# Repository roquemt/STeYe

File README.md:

# STeYe
Flight computer for rocket competition. 

This flight computer is designed for high-performance rocketry competitions, offering precise measurement and control for various flight parameters. The system integrates a range of sensors and features to ensure reliable data acquisition and communication throughout the flight. It is built with flexibility, durability, and scalability in mind for a variety of mission profiles.

Key Features:

-  Accelerometers: Dual-range accelerometers (+/-16g and +/-200g) for accurate low and high-g-force measurement during flight.
-  Pressure Sensor: Atmospheric pressure monitoring for altitude and environmental data.
-  Humidity & Temperature Sensor: Measures environmental conditions critical for flight analysis.
-  Magnetometer: Provides orientation and heading information by sensing the Earth’s magnetic field.
-  Current Sensor: Tracks power consumption for optimized energy management.
-  Camera Interface (FPC): Supports OV5640 camera for video and image capture during flight.
-  WiFi & Bluetooth: Wireless communication for data transfer and real-time telemetry.
-  GNSS (Global Navigation Satellite System): Provides accurate positioning data for tracking and flight path monitoring.
-  LoRa: Long-range, low-power communication capability for telemetry.
-  Pyro Channel: Single pyro channel for controlled deployment of parachutes or other pyrotechnic devices.
-  Motor Control: Supports either one dual-coil stepper motor or up to four servomotors, operating between 5V and 12V for mechanical actuation.
-  Passive Buzzer: Provides audio alerts for critical status or events.
-  LED Indicators: Visual feedback for power, status, and activity.
-  Memory: Includes both flash storage and microSD for data logging and flight data retention.

Carrier Board (sensors and peripherals)

M.2 Board (Microcontrollers and Wifi)

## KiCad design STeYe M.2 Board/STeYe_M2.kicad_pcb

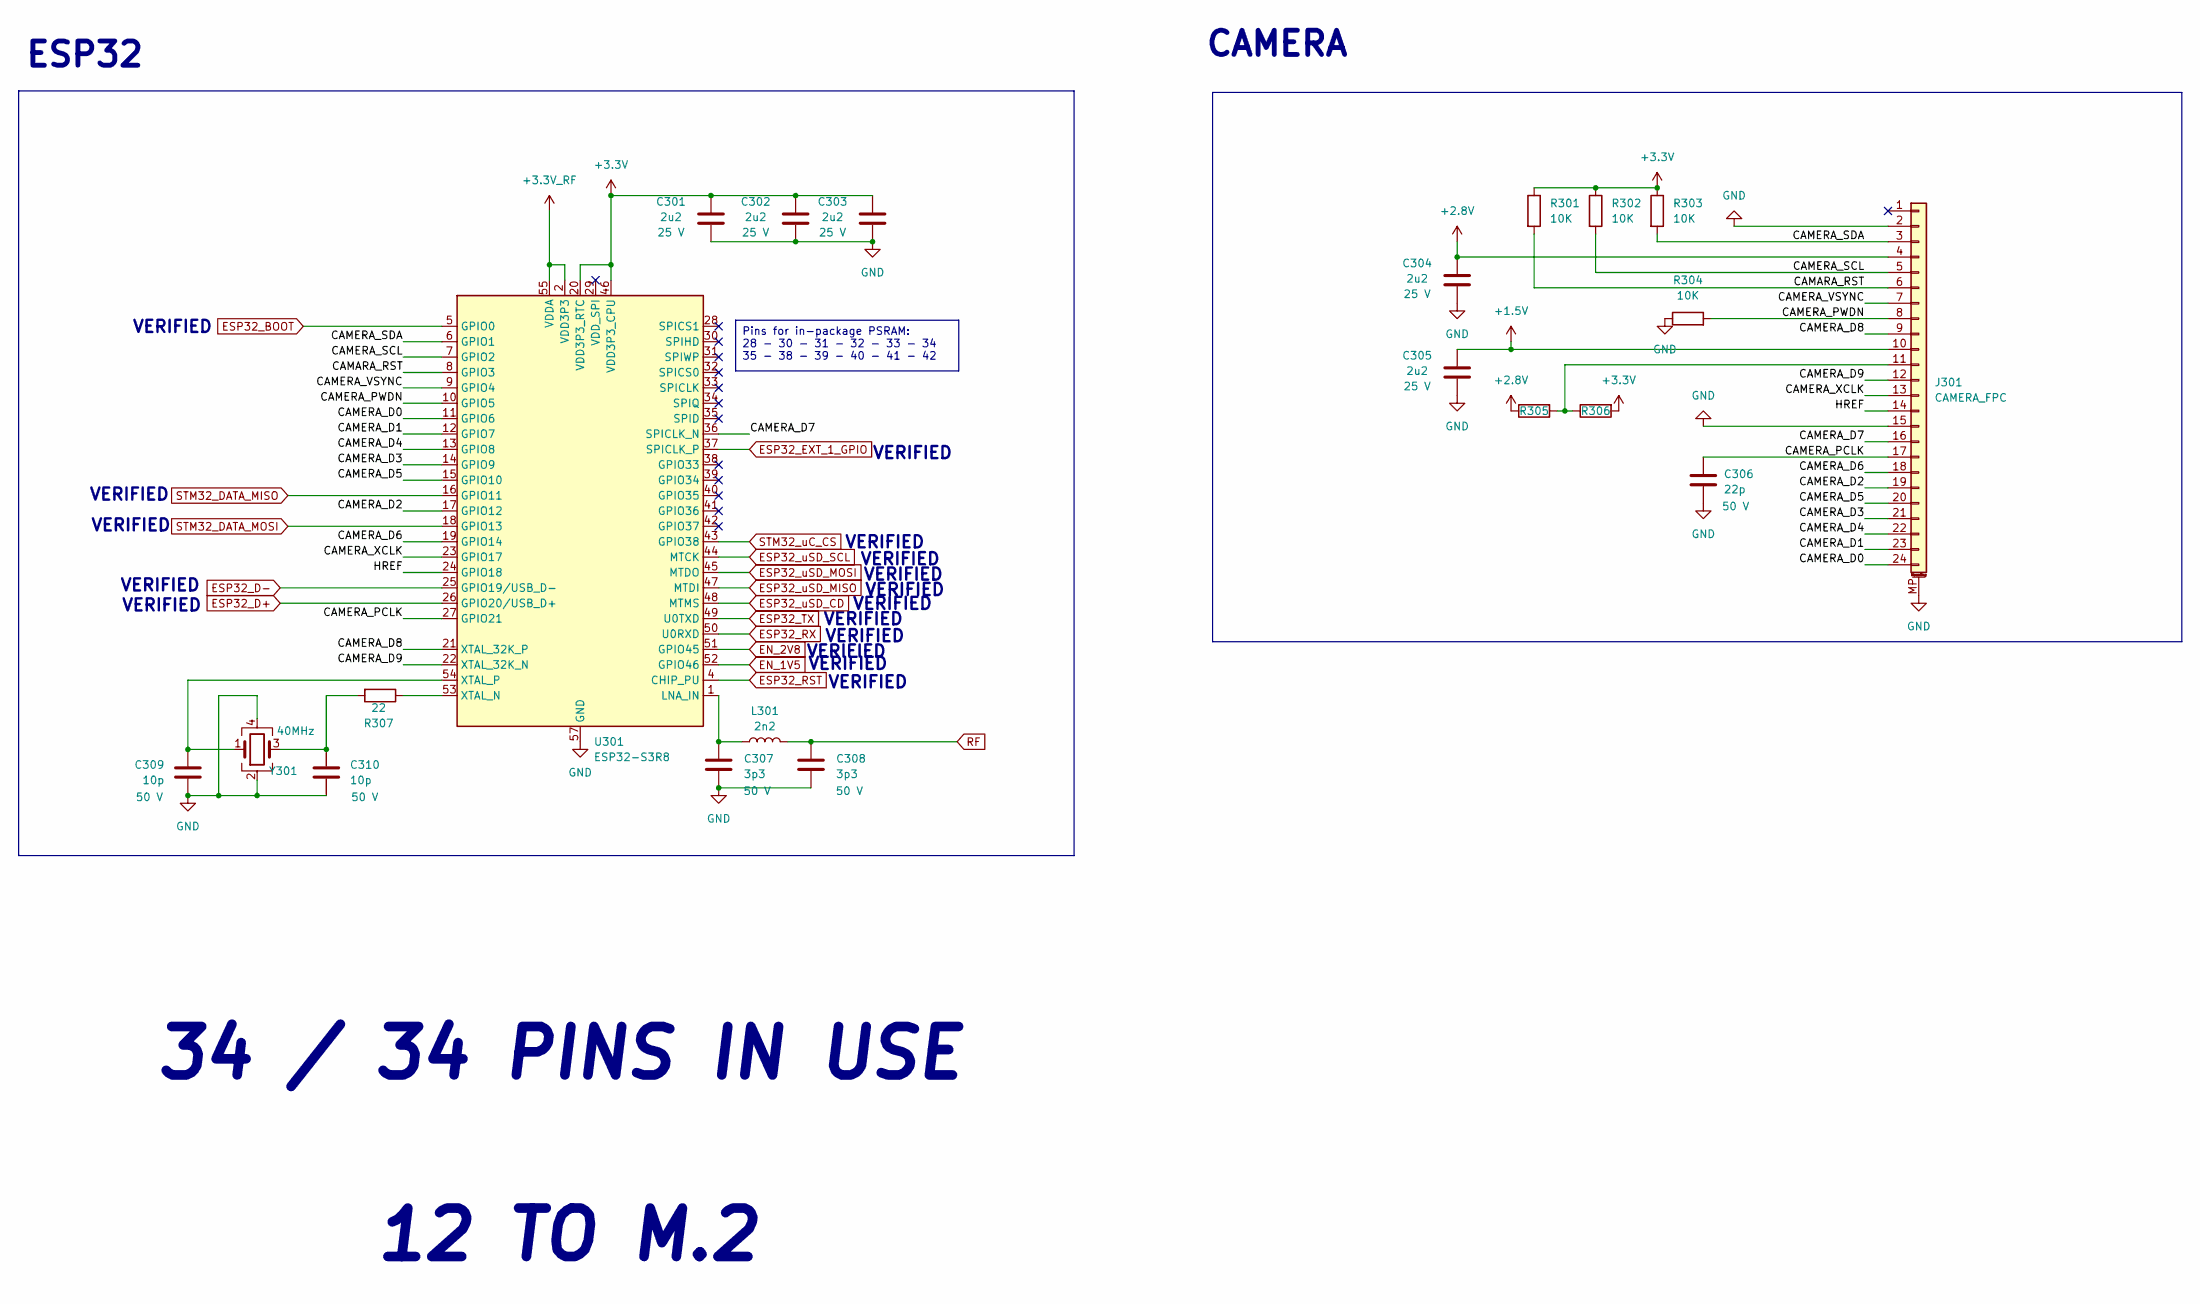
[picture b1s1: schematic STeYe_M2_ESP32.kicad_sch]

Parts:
C301, C302, C303, C304, C305: 2u2; C_0402_1005Metric; Voltage 25 V
C306: 22p; C_0402_1005Metric; Voltage 50 V
C307, C308: 3p3; C_0402_1005Metric; Voltage 50 V
C309, C310: 10p; C_0402_1005Metric; Voltage 50 V
J301: CAMERA_FPC; Hirose_FH12-24S-0.5SH_1x24-1MP_P0.50mm_Horizontal
L301: 2n2; Inductor
R301, R302, R303, R304: 10K; R_0402_1005Metric
R305, R306: R_0402_1005Metric
R307: 22; R_0402_1005Metric
U301: ESP32-S3R8; QFN-56-1EP_7x7mm_P0.4mm_EP4x4mm
Y301: 40MHz; Crystal_SMD_2016-4Pin_2.0x1.6mm

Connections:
+1.5V: C305.2, J301.10; also elsewhere on the board
+2.8V: C304.2, J301.4, R305.1; also elsewhere on the board
+3.3V: C301.2, C302.2, C303.2, R301.1, R302.1, R303.1, R306.2, U301.20 (VDD3P3_RTC), U301.46 (VDD3P3_CPU); also elsewhere on the board
+3.3V_RF: U301.2 (VDD3P3), U301.3 (VDD3P3), U301.55 (VDDA), U301.56 (VDDA); also elsewhere on the board
/ESP32/CAMARA_RST: J301.6, R301.2, U301.8 (GPIO3)
/ESP32/CAMERA_D0: J301.24, U301.11 (GPIO6)
/ESP32/CAMERA_D1: J301.23, U301.12 (GPIO7)
/ESP32/CAMERA_D2: J301.19, U301.17 (GPIO12)
/ESP32/CAMERA_D3: J301.21, U301.14 (GPIO9)
/ESP32/CAMERA_D4: J301.22, U301.13 (GPIO8)
/ESP32/CAMERA_D5: J301.20, U301.15 (GPIO10)
/ESP32/CAMERA_D6: J301.18, U301.19 (GPIO14)
/ESP32/CAMERA_D7: J301.16, U301.36 (SPICLK_N)
/ESP32/CAMERA_D8: J301.9, U301.21 (XTAL_32K_P)
/ESP32/CAMERA_D9: J301.12, U301.22 (XTAL_32K_N)
/ESP32/CAMERA_PCLK: C306.2, J301.17, U301.27 (GPIO21)
/ESP32/CAMERA_PWDN: J301.8, R304.2, U301.10 (GPIO5)
/ESP32/CAMERA_SCL: J301.5, R302.2, U301.7 (GPIO2)
/ESP32/CAMERA_SDA: J301.3, R303.2, U301.6 (GPIO1)
/ESP32/CAMERA_VSYNC: J301.7, U301.9 (GPIO4)
/ESP32/CAMERA_XCLK: J301.13, U301.23 (GPIO17)
/ESP32/HREF: J301.14, U301.24 (GPIO18)
EN_1V5: U301.52 (GPIO46); also elsewhere on the board
EN_2V8: U301.51 (GPIO45); also elsewhere on the board
ESP32_BOOT: U301.5 (GPIO0); also elsewhere on the board
ESP32_D+: U301.26 (GPIO20/USB_D+); also elsewhere on the board
ESP32_D-: U301.25 (GPIO19/USB_D-); also elsewhere on the board
ESP32_EXT_1_GPIO: U301.37 (SPICLK_P); also elsewhere on the board
ESP32_RST: U301.4 (CHIP_PU); also elsewhere on the board
ESP32_RX: U301.50 (U0RXD); also elsewhere on the board
ESP32_TX: U301.49 (U0TXD); also elsewhere on the board
ESP32_uSD_CD: U301.48 (MTMS); also elsewhere on the board
ESP32_uSD_MISO: U301.47 (MTDI); also elsewhere on the board
ESP32_uSD_MOSI: U301.45 (MTDO); also elsewhere on the board
ESP32_uSD_SCL: U301.44 (MTCK); also elsewhere on the board
GND: C301.1, C302.1, C303.1, C304.1, C305.1, C306.1, C307.2, C308.2, C309.2, C310.2, J301.2, J301.15, J301.MP (MountPin), R304.1, U301.57 (GND), Y301.2, Y301.4; also elsewhere on the board
unnamed: C310.1, R307.2, Y301.3
unnamed: J301.11, R305.2, R306.1
unnamed: C307.1, L301.1, U301.1 (LNA_IN)
unnamed: R307.1, U301.53 (XTAL_N)
unnamed: C309.1, U301.54 (XTAL_P), Y301.1
RF: C308.1, L301.2; also elsewhere on the board
STM32_DATA_MISO: U301.16 (GPIO11); also elsewhere on the board
STM32_DATA_MOSI: U301.18 (GPIO13); also elsewhere on the board
STM32_uC_CS: U301.43 (GPIO38); also elsewhere on the board

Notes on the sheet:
Pins for in-package PSRAM: 28 - 30 - 31 - 32 - 33 - 34 35 - 38 - 39 - 40 - 41 - 42
ESP32
VERIFIED
12 TO M.2
CAMERA
34 / 34 PINS IN USE

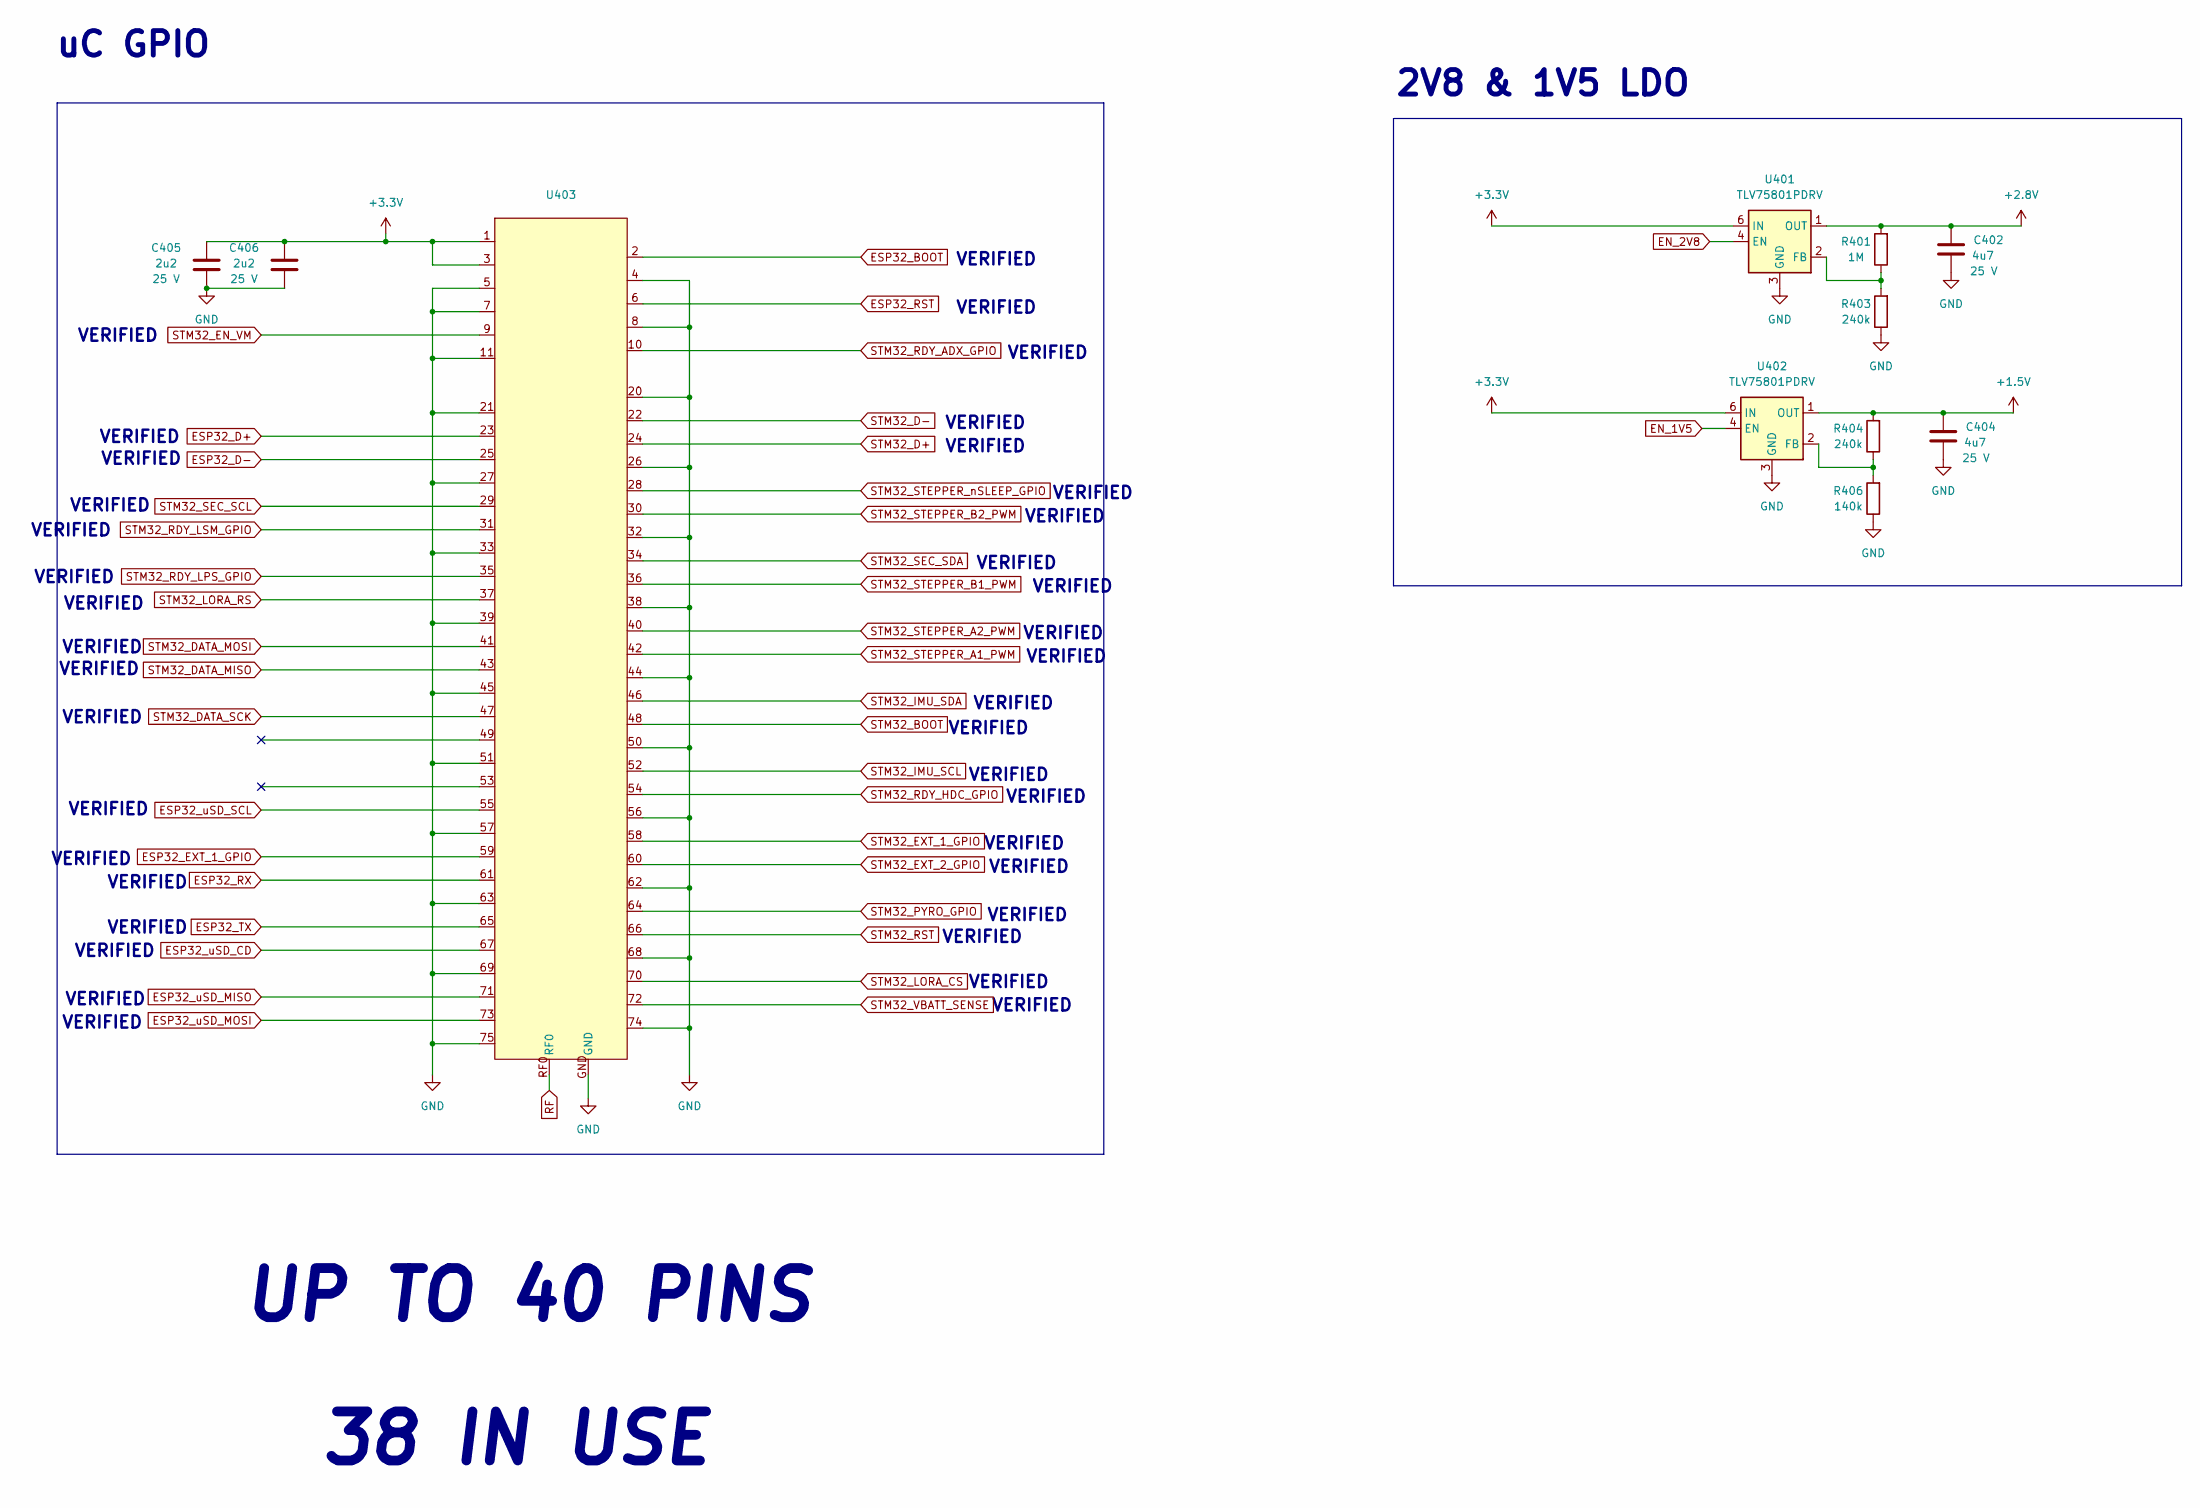
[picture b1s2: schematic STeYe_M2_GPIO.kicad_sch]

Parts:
C402, C404: 4u7; C_0402_1005Metric; Voltage 25 V
C405, C406: 2u2; C_0402_1005Metric; Voltage 25 V
R401: 1M; R_0402_1005Metric
R403, R404: 240k; R_0402_1005Metric
R406: 140k; R_0402_1005Metric
U401, U402: TLV75801PDRV; WSON-6-1EP_2x2mm_P0.65mm_EP1x1.6mm
U403: M.2-B-KEY_Antenna_1

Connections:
+1.5V: C404.1, R404.2, U402.1 (OUT); also elsewhere on the board
+2.8V: C402.1, R401.2, U401.1 (OUT); also elsewhere on the board
+3.3V: C405.2, C406.2, U401.6 (IN), U402.6 (IN), U403.1, U403.3; also elsewhere on the board
EN_1V5: U402.4 (EN); also elsewhere on the board
EN_2V8: U401.4 (EN); also elsewhere on the board
ESP32_BOOT: U403.2; also elsewhere on the board
ESP32_D+: U403.23; also elsewhere on the board
ESP32_D-: U403.25; also elsewhere on the board
ESP32_EXT_1_GPIO: U403.59; also elsewhere on the board
ESP32_RST: U403.6; also elsewhere on the board
ESP32_RX: U403.61; also elsewhere on the board
ESP32_TX: U403.65; also elsewhere on the board
ESP32_uSD_CD: U403.67; also elsewhere on the board
ESP32_uSD_MISO: U403.71; also elsewhere on the board
ESP32_uSD_MOSI: U403.73; also elsewhere on the board
ESP32_uSD_SCL: U403.55; also elsewhere on the board
GND: C402.2, C404.2, C405.1, C406.1, R403.1, R406.1, U401.3 (GND), U401.7 (GND), U402.3 (GND), U402.7 (GND), U403.4, U403.5, U403.7, U403.8, U403.11, U403.20, U403.21, U403.26, U403.27, U403.32, U403.33, U403.38, U403.39, U403.44, U403.45, U403.50, U403.51, U403.56, U403.57, U403.62, U403.63, U403.68, U403.69, U403.74, U403.75, U403.GND; also elsewhere on the board
unnamed: R401.1, R403.2, U401.2 (FB)
unnamed: R404.1, R406.2, U402.2 (FB)
RF: U403.RF0; also elsewhere on the board
STM32_BOOT: U403.48; also elsewhere on the board
STM32_D+: U403.24; also elsewhere on the board
STM32_D-: U403.22; also elsewhere on the board
STM32_DATA_MISO: U403.43; also elsewhere on the board
STM32_DATA_MOSI: U403.41; also elsewhere on the board
STM32_DATA_SCK: U403.47; also elsewhere on the board
STM32_EN_VM: U403.9; also elsewhere on the board
STM32_EXT_1_GPIO: U403.58; also elsewhere on the board
STM32_EXT_2_GPIO: U403.60; also elsewhere on the board
STM32_IMU_SCL: U403.52; also elsewhere on the board
STM32_IMU_SDA: U403.46; also elsewhere on the board
STM32_LORA_CS: U403.70; also elsewhere on the board
STM32_LORA_RS: U403.37; also elsewhere on the board
STM32_PYRO_GPIO: U403.64; also elsewhere on the board
STM32_RDY_ADX_GPIO: U403.10; also elsewhere on the board
STM32_RDY_HDC_GPIO: U403.54; also elsewhere on the board
STM32_RDY_LPS_GPIO: U403.35; also elsewhere on the board
STM32_RDY_LSM_GPIO: U403.31; also elsewhere on the board
STM32_RST: U403.66; also elsewhere on the board
STM32_SEC_SCL: U403.29; also elsewhere on the board
STM32_SEC_SDA: U403.34; also elsewhere on the board
STM32_STEPPER_A1_PWM: U403.42; also elsewhere on the board
STM32_STEPPER_A2_PWM: U403.40; also elsewhere on the board
STM32_STEPPER_B1_PWM: U403.36; also elsewhere on the board
STM32_STEPPER_B2_PWM: U403.30; also elsewhere on the board
STM32_STEPPER_nSLEEP_GPIO: U403.28; also elsewhere on the board
STM32_VBATT_SENSE: U403.72; also elsewhere on the board

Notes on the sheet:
VERIFIED
UP TO 40 PINS
uC GPIO
2V8 & 1V5 LDO
38 IN USE

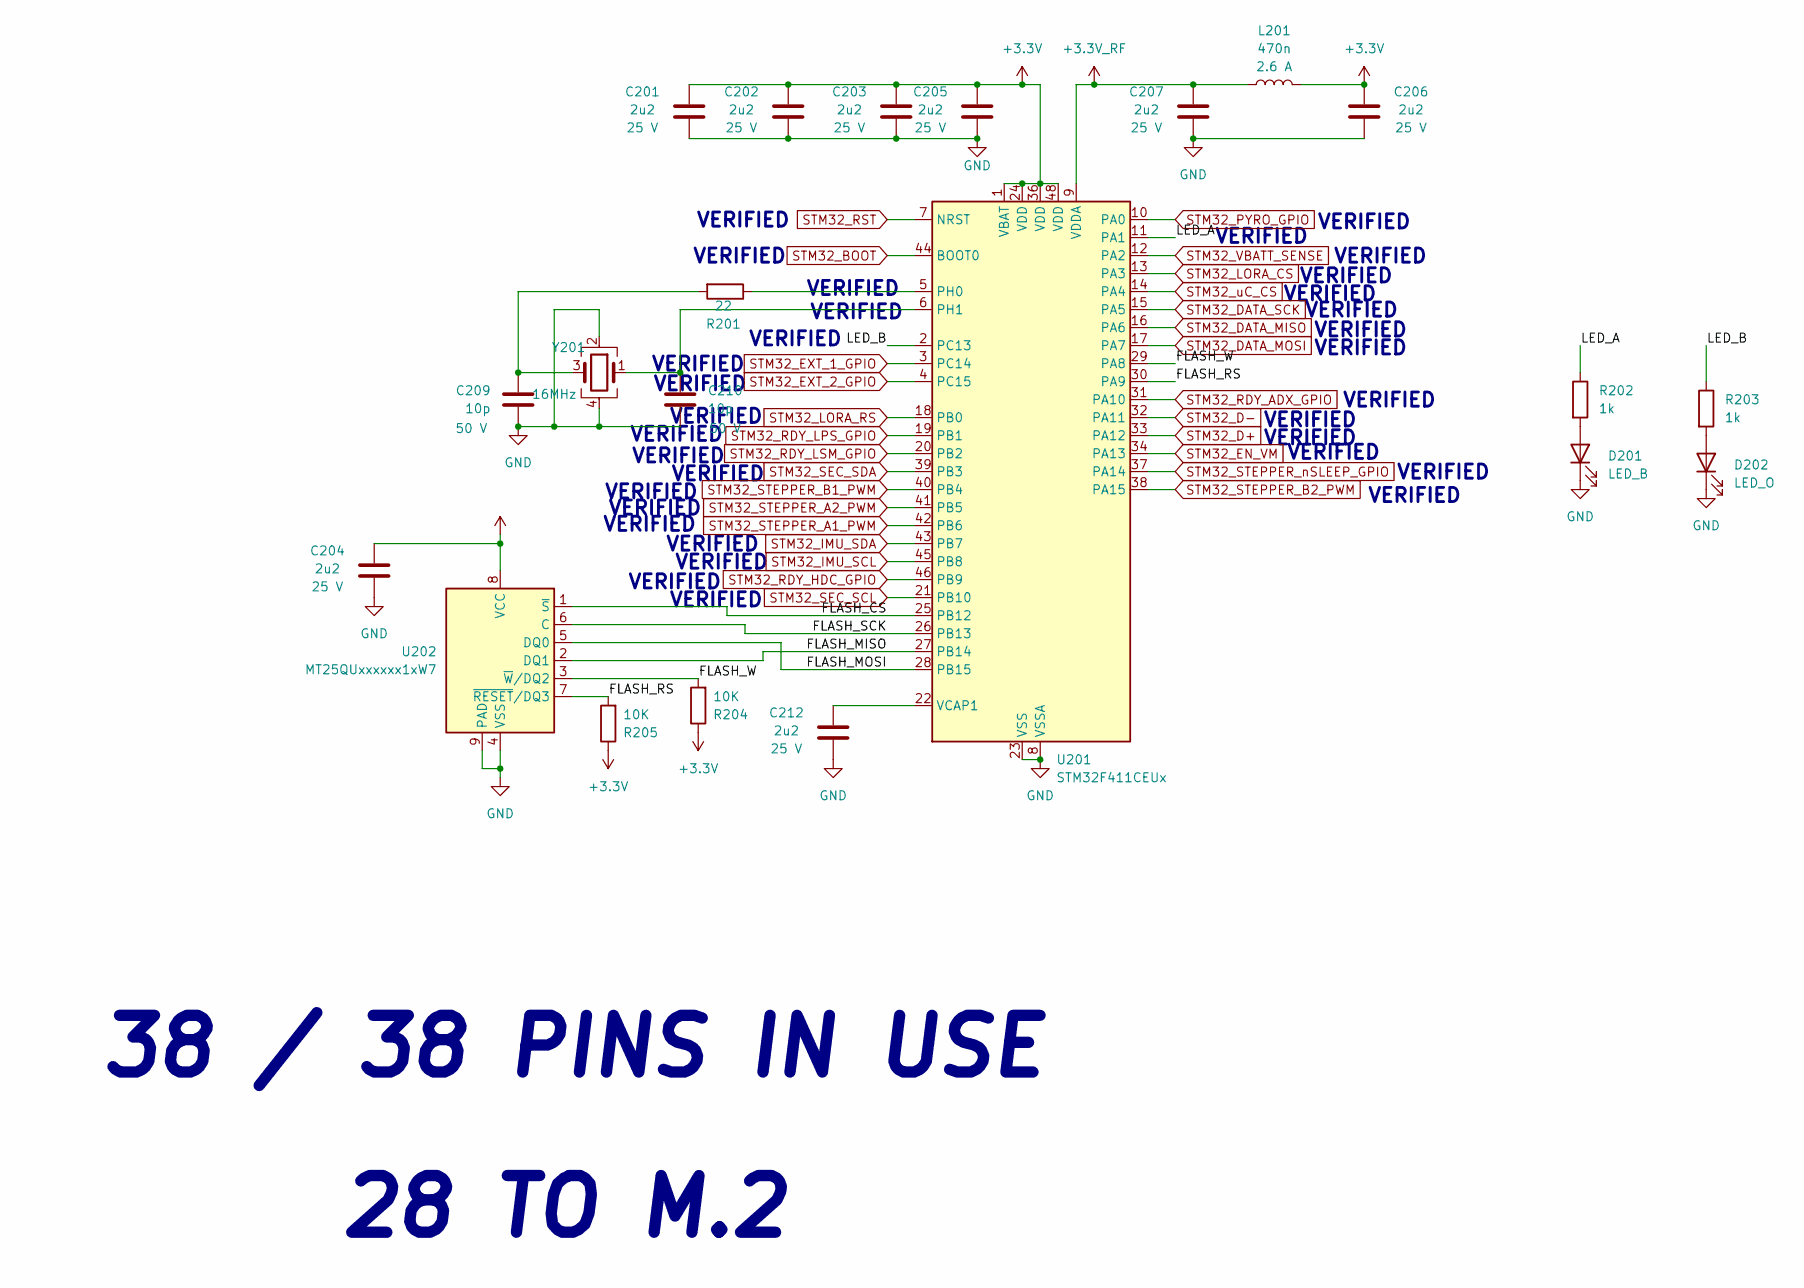
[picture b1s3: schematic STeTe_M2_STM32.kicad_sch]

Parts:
C201, C202, C203, C204, C205, C206, C207, C212: 2u2; C_0402_1005Metric; Voltage 25 V
C209, C210: 10p; C_0402_1005Metric; Voltage 50 V
D201: LED_B; D_0603_1608Metric
D202: LED_O; D_0603_1608Metric
L201: 470n; L_0603_1608Metric
R201: 22; R_0402_1005Metric
R202, R203: 1k; R_0402_1005Metric
R204, R205: 10K; R_0402_1005Metric
U201: STM32F411CEUx; QFN-48-1EP_7x7mm_P0.5mm_EP5.6x5.6mm
U202: MT25QUxxxxxx1xW7; W-PDFN-8-1EP_6x5mm_P1.27mm_EP3x3mm
Y201: 16MHz; Crystal_SMD_2016-4Pin_2.0x1.6mm

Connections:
+3.3V: C201.2, C202.2, C203.2, C204.2, C205.2, C206.2, L201.2, R204.1, R205.1, U201.1 (VBAT), U201.24 (VDD), U201.36 (VDD), U201.48 (VDD), U202.8 (VCC); also elsewhere on the board
+3.3V_RF: C207.2, L201.1, U201.9 (VDDA); also elsewhere on the board
/STM32/FLASH_CS: U201.25 (PB12), U202.1 (~S)
/STM32/FLASH_MISO: U201.27 (PB14), U202.2 (DQ1)
/STM32/FLASH_MOSI: U201.28 (PB15), U202.5 (DQ0)
/STM32/FLASH_RS: R205.2, U201.30 (PA9), U202.7 (~RESET/DQ3)
/STM32/FLASH_SCK: U201.26 (PB13), U202.6 (C)
/STM32/FLASH_W: R204.2, U201.29 (PA8), U202.3 (~W/DQ2)
/STM32/LED_A: R202.1, U201.11 (PA1)
/STM32/LED_B: R203.1, U201.2 (PC13)
GND: C201.1, C202.1, C203.1, C204.1, C205.1, C206.1, C207.1, C209.2, C210.2, C212.1, D201.1 (K), D202.1 (K), U201.8 (VSSA), U201.23 (VSS), U201.35 (VSS), U201.47 (VSS), U201.49 (VSS), U202.4 (VSS), U202.9 (PAD), Y201.2, Y201.4; also elsewhere on the board
unnamed: C209.1, R201.2, Y201.3
unnamed: D201.2 (A), R202.2
unnamed: D202.2 (A), R203.2
unnamed: R201.1, U201.5 (PH0)
unnamed: C210.1, U201.6 (PH1), Y201.1
unnamed: C212.2, U201.22 (VCAP1)
STM32_BOOT: U201.44 (BOOT0); also elsewhere on the board
STM32_D+: U201.33 (PA12); also elsewhere on the board
STM32_D-: U201.32 (PA11); also elsewhere on the board
STM32_DATA_MISO: U201.16 (PA6); also elsewhere on the board
STM32_DATA_MOSI: U201.17 (PA7); also elsewhere on the board
STM32_DATA_SCK: U201.15 (PA5); also elsewhere on the board
STM32_EN_VM: U201.34 (PA13); also elsewhere on the board
STM32_EXT_1_GPIO: U201.3 (PC14); also elsewhere on the board
STM32_EXT_2_GPIO: U201.4 (PC15); also elsewhere on the board
STM32_IMU_SCL: U201.45 (PB8); also elsewhere on the board
STM32_IMU_SDA: U201.43 (PB7); also elsewhere on the board
STM32_LORA_CS: U201.13 (PA3); also elsewhere on the board
STM32_LORA_RS: U201.18 (PB0); also elsewhere on the board
STM32_PYRO_GPIO: U201.10 (PA0); also elsewhere on the board
STM32_RDY_ADX_GPIO: U201.31 (PA10); also elsewhere on the board
STM32_RDY_HDC_GPIO: U201.46 (PB9); also elsewhere on the board
STM32_RDY_LPS_GPIO: U201.19 (PB1); also elsewhere on the board
STM32_RDY_LSM_GPIO: U201.20 (PB2); also elsewhere on the board
STM32_RST: U201.7 (NRST); also elsewhere on the board
STM32_SEC_SCL: U201.21 (PB10); also elsewhere on the board
STM32_SEC_SDA: U201.39 (PB3); also elsewhere on the board
STM32_STEPPER_A1_PWM: U201.42 (PB6); also elsewhere on the board
STM32_STEPPER_A2_PWM: U201.41 (PB5); also elsewhere on the board
STM32_STEPPER_B1_PWM: U201.40 (PB4); also elsewhere on the board
STM32_STEPPER_B2_PWM: U201.38 (PA15); also elsewhere on the board
STM32_STEPPER_nSLEEP_GPIO: U201.37 (PA14); also elsewhere on the board
STM32_VBATT_SENSE: U201.12 (PA2); also elsewhere on the board
STM32_uC_CS: U201.14 (PA4); also elsewhere on the board

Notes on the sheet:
VERIFIED
28 TO M.2
38 / 38 PINS IN USE

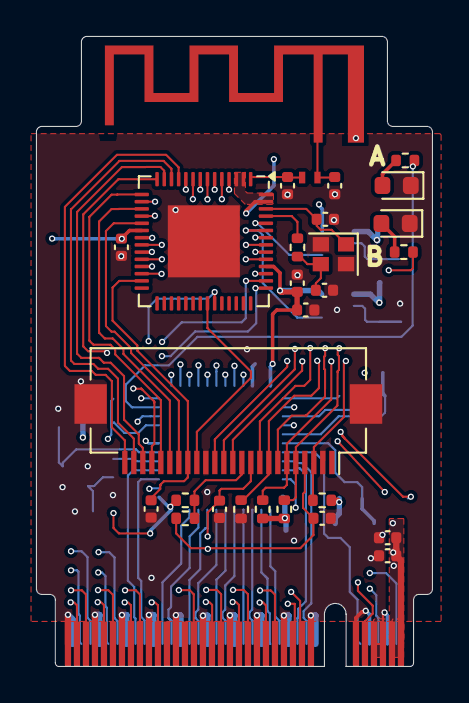
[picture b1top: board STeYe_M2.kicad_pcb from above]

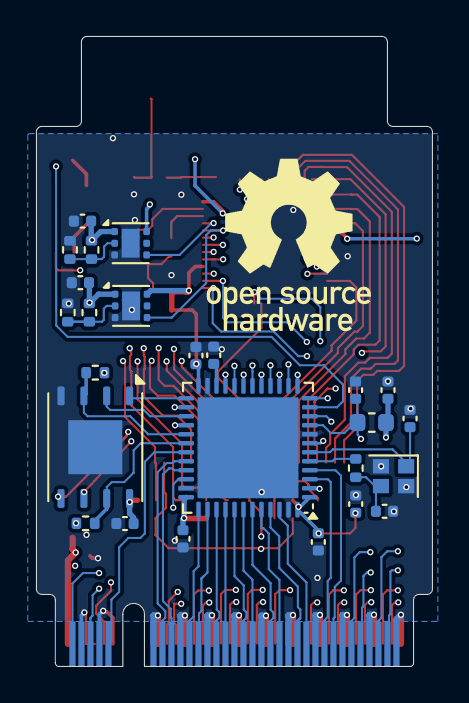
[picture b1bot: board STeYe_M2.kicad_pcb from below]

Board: 8 copper layers, 22.0 x 35.0 mm, 53 parts (25 on the bottom side), 86 nets.

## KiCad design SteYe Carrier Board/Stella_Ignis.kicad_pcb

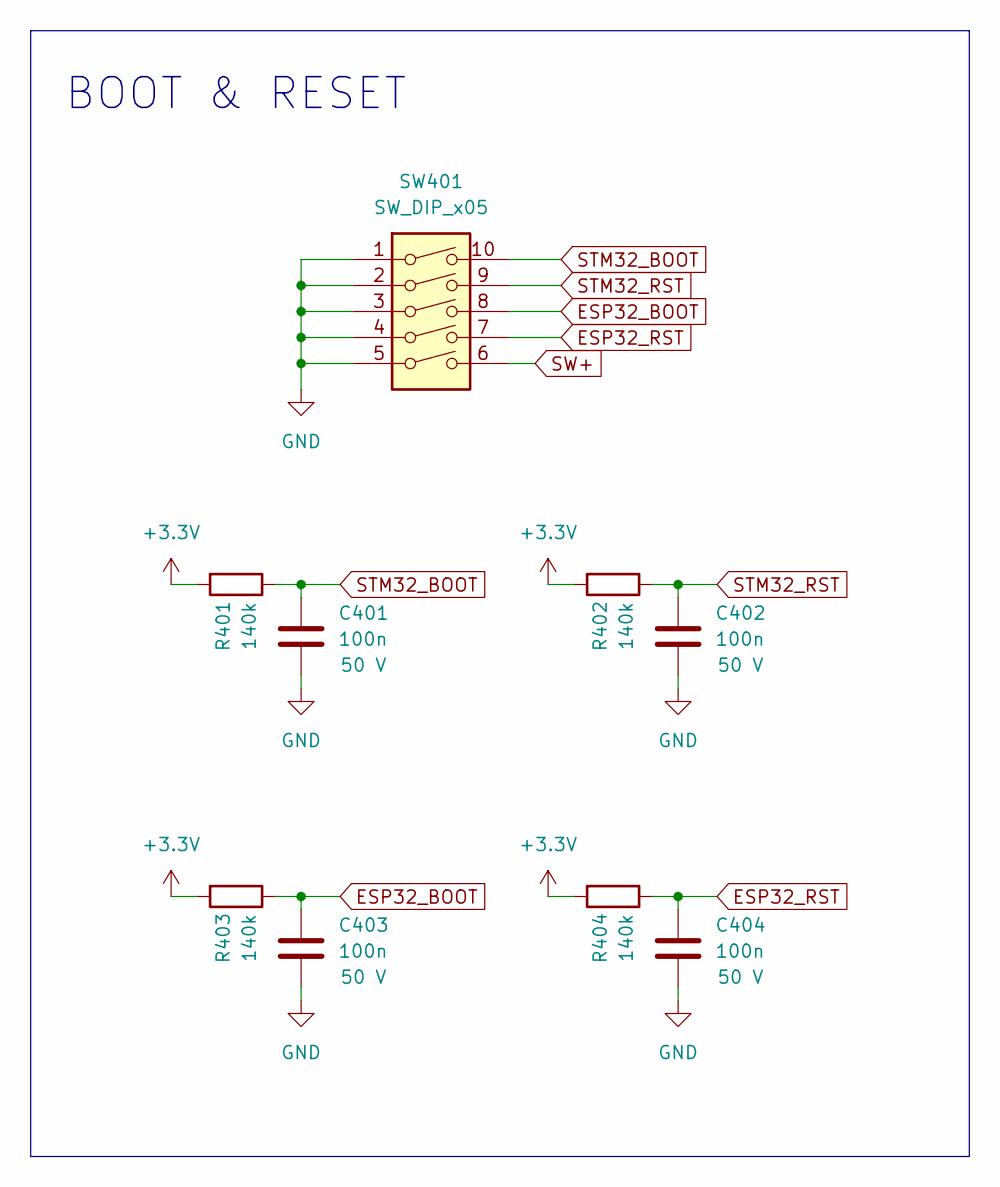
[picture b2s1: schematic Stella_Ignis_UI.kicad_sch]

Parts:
C401, C402, C403, C404: 100n; C_0402_1005Metric; Voltage 50 V
R401, R402, R403, R404: 140k; R_0402_1005Metric
SW401: SW_DIP_x05; SW_DIP_SPSTx05_Slide_6.7x14.26mm_W8.61mm_P2.54mm_LowProfile

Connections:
+3.3V: R401.2, R402.2, R403.2, R404.2; also elsewhere on the board
ESP32_BOOT: C403.1, R403.1, SW401.8; also elsewhere on the board
ESP32_RST: C404.1, R404.1, SW401.7; also elsewhere on the board
GND: C401.2, C402.2, C403.2, C404.2, SW401.1, SW401.2, SW401.3, SW401.4, SW401.5; also elsewhere on the board
STM32_BOOT: C401.1, R401.1, SW401.10; also elsewhere on the board
STM32_RST: C402.1, R402.1, SW401.9; also elsewhere on the board
SW+: SW401.6; also elsewhere on the board

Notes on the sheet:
BOOT & RESET
